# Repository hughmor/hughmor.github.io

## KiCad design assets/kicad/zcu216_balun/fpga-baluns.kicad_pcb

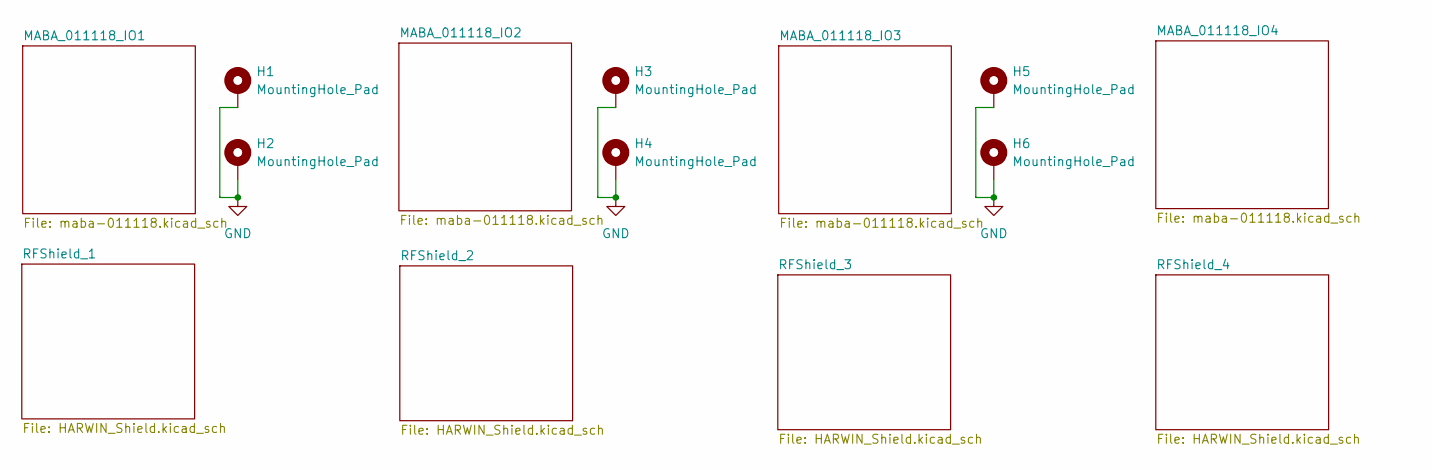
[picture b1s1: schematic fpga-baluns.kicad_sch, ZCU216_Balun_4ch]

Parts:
H1, H2, H3, H4, H5, H6: MountingHole_Pad; MountingHole_3.2mm_M3_DIN965_Pad_TopOnly

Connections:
GND: H1.1, H2.1, H3.1, H4.1, H5.1, H6.1; also elsewhere on the board

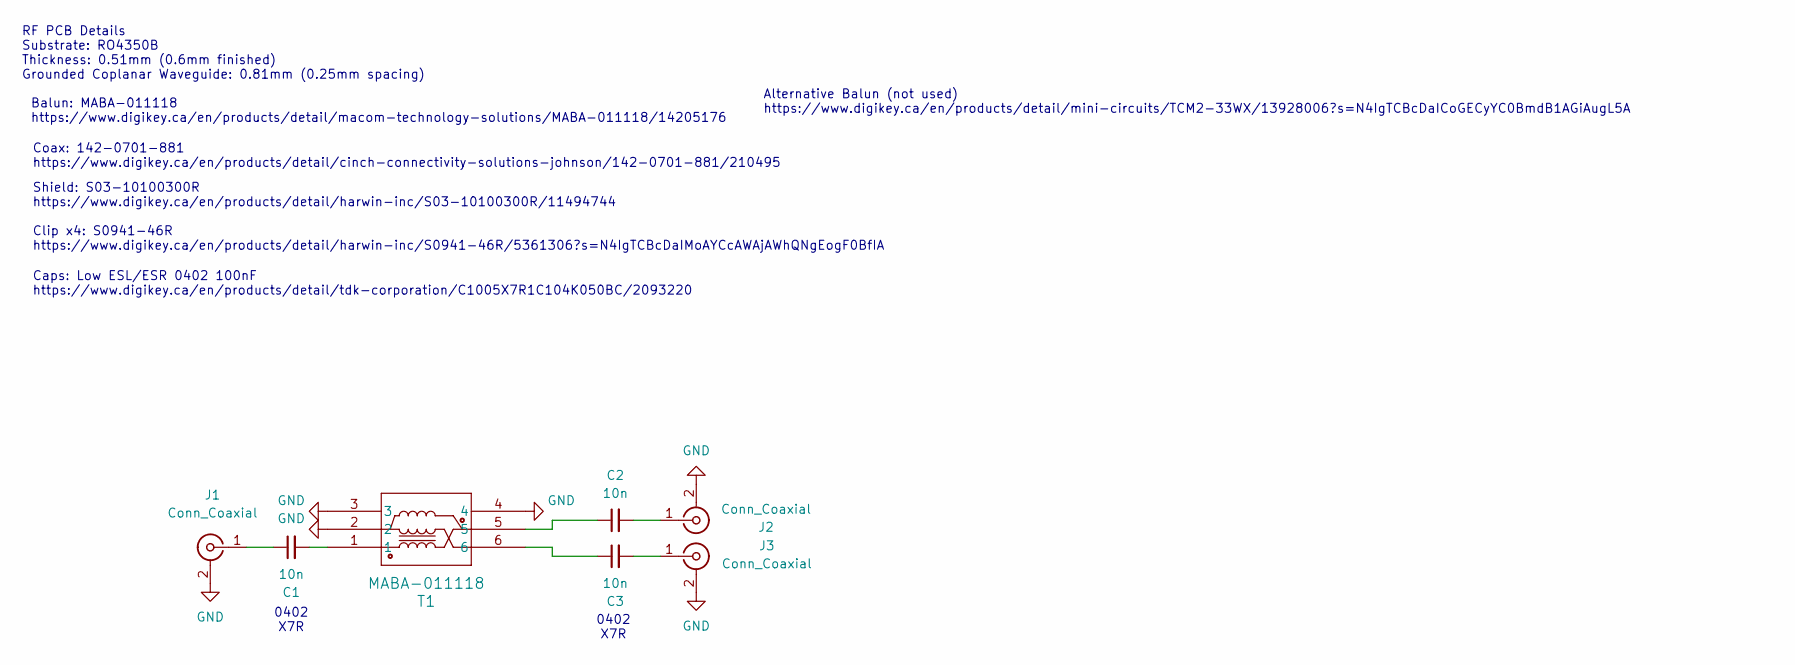
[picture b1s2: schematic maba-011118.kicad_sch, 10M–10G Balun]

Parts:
C1, C2, C3: 10n; C_0402_1005Metric; LCSC Part # C3855387
J1, J2, J3: Conn_Coaxial; SMA_Molex_73251-1153_EdgeMount_Horizontal_Custom
T1: MABA-011118; MABA-011118_MCM; LCSC Part # C50327609

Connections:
GND: J1.2 (Ext), J2.2 (Ext), J3.2 (Ext), T1.2, T1.3, T1.4; also elsewhere on the board
unnamed: C1.2, T1.1
unnamed: C2.1, T1.5
unnamed: C3.1, T1.6
unnamed: C1.1, J1.1 (In)
unnamed: C2.2, J2.1 (In)
unnamed: C3.2, J3.1 (In)

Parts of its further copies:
C4, C5, C6, C7, C8, C9, C10, C11, C12: 10n; C_0402_1005Metric; LCSC Part # C3855387
J4, J5, J6, J7, J8, J9, J10, J11, J12: Conn_Coaxial; SMA_Molex_73251-1153_EdgeMount_Horizontal_Custom
T2, T3, T4: MABA-011118; MABA-011118_MCM; LCSC Part # C50327609

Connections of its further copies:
GND: J4.2 (Ext), J5.2 (Ext), J6.2 (Ext), J7.2 (Ext), J8.2 (Ext), J9.2 (Ext), J10.2 (Ext), J11.2 (Ext), J12.2 (Ext), T2.2, T2.3, T2.4, T3.2, T3.3, T3.4, T4.2, T4.3, T4.4; also elsewhere on the board
unnamed: C4.2, T2.1
unnamed: C5.1, T2.5
unnamed: C6.1, T2.6
unnamed: C7.2, T3.1
unnamed: C8.1, T3.5
unnamed: C9.1, T3.6
unnamed: C10.2, T4.1
unnamed: C11.1, T4.5
unnamed: C12.1, T4.6
unnamed: C4.1, J4.1 (In)
unnamed: C5.2, J5.1 (In)
unnamed: C6.2, J6.1 (In)
unnamed: C7.1, J7.1 (In)
unnamed: C8.2, J8.1 (In)
unnamed: C9.2, J9.1 (In)
unnamed: C10.1, J10.1 (In)
unnamed: C11.2, J11.1 (In)
unnamed: C12.2, J12.1 (In)

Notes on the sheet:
0402 X7R
Alternative Balun (not used) https://www.digikey.ca/en/products/detail/mini-circuits/TCM2-33WX/13928006?s=N4IgTCBcDaICoGECyYC0BmdB1AGiAugL5A
Balun: MABA-011118 https://www.digikey.ca/en/products/detail/macom-technology-solutions/MABA-011118/14205176
Coax: 142-0701-881 https://www.digikey.ca/en/products/detail/cinch-connectivity-solutions-johnson/142-0701-881/210495
RF PCB Details Substrate: RO4350B Thickness: 0.51mm (0.6mm finished) Grounded Coplanar Waveguide: 0.81mm (0.25mm spacing)
Caps: Low ESL/ESR 0402 100nF https://www.digikey.ca/en/products/detail/tdk-corporation/C1005X7R1C104K050BC/2093220
Shield: S03-10100300R https://www.digikey.ca/en/products/detail/harwin-inc/S03-10100300R/11494744 Clip x4: S0941-46R https://www.digikey.ca/en/products/detail/harwin-inc/S0941-46R/5361306?s=N4IgTCBcDaIMoAYCcAWAjAWhQNgEogF0BfIA

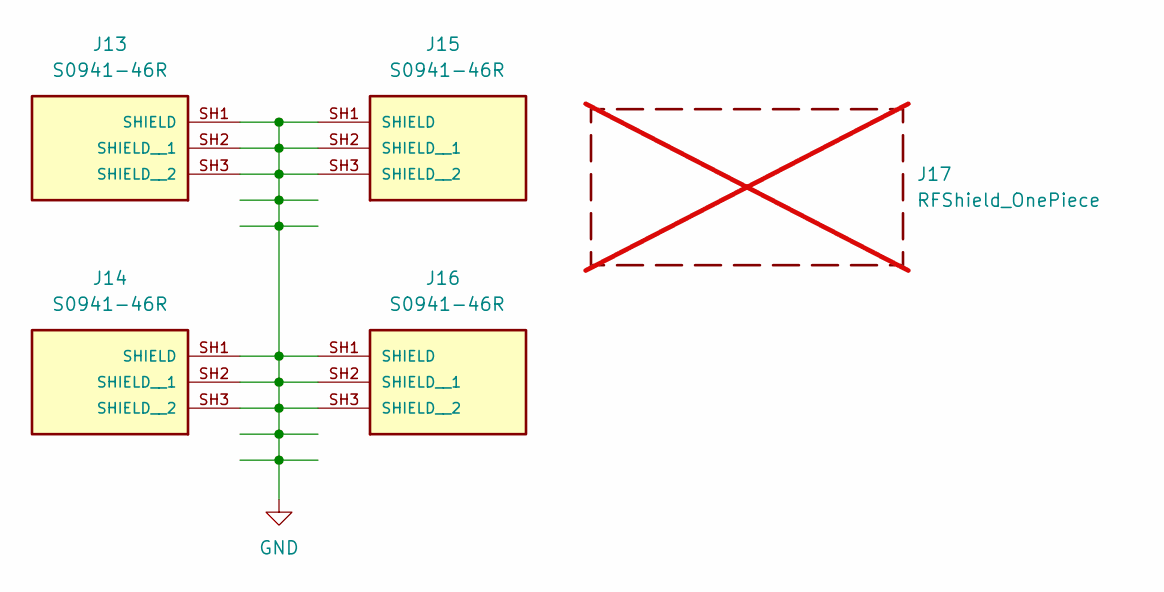
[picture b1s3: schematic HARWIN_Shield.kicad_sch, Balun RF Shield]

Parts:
J13, J14, J15, J16: S0941-46R; HARWIN_S1001-46R; PARTREV 5; LCSC Part # C5440762
J17: RFShield_OnePiece; HARWIN_S03_10100300R; not fitted

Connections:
GND: J13.SH1 (SHIELD), J13.SH2 (SHIELD__1), J13.SH3 (SHIELD__2), J14.SH1 (SHIELD), J14.SH2 (SHIELD__1), J14.SH3 (SHIELD__2), J15.SH1 (SHIELD), J15.SH2 (SHIELD__1), J15.SH3 (SHIELD__2), J16.SH1 (SHIELD), J16.SH2 (SHIELD__1), J16.SH3 (SHIELD__2); also elsewhere on the board

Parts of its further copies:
J18, J19, J20, J21, J23, J24, J25, J26, J28, J29, J30, J31: S0941-46R; HARWIN_S1001-46R; PARTREV 5; LCSC Part # C5440762
J22, J27, J32: RFShield_OnePiece; HARWIN_S03_10100300R; not fitted

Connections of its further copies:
GND: J18.SH1 (SHIELD), J18.SH2 (SHIELD__1), J18.SH3 (SHIELD__2), J19.SH1 (SHIELD), J19.SH2 (SHIELD__1), J19.SH3 (SHIELD__2), J20.SH1 (SHIELD), J20.SH2 (SHIELD__1), J20.SH3 (SHIELD__2), J21.SH1 (SHIELD), J21.SH2 (SHIELD__1), J21.SH3 (SHIELD__2), J23.SH1 (SHIELD), J23.SH2 (SHIELD__1), J23.SH3 (SHIELD__2), J24.SH1 (SHIELD), J24.SH2 (SHIELD__1), J24.SH3 (SHIELD__2), J25.SH1 (SHIELD), J25.SH2 (SHIELD__1), J25.SH3 (SHIELD__2), J26.SH1 (SHIELD), J26.SH2 (SHIELD__1), J26.SH3 (SHIELD__2), J28.SH1 (SHIELD), J28.SH2 (SHIELD__1), J28.SH3 (SHIELD__2), J29.SH1 (SHIELD), J29.SH2 (SHIELD__1), J29.SH3 (SHIELD__2), J30.SH1 (SHIELD), J30.SH2 (SHIELD__1), J30.SH3 (SHIELD__2), J31.SH1 (SHIELD), J31.SH2 (SHIELD__1), J31.SH3 (SHIELD__2); also elsewhere on the board

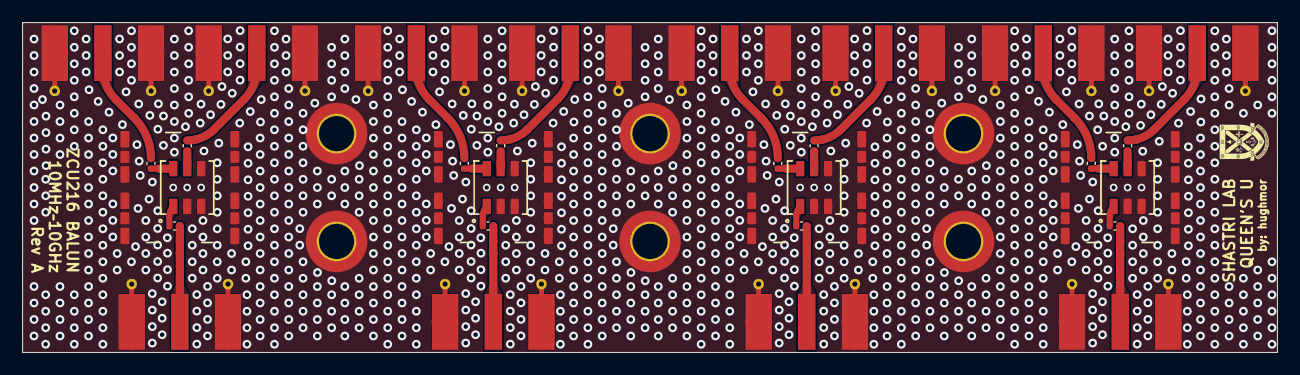
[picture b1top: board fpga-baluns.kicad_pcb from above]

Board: 2 copper layers, 114.1 x 30.0 mm, 54 parts (0 on the bottom side), 25 nets.

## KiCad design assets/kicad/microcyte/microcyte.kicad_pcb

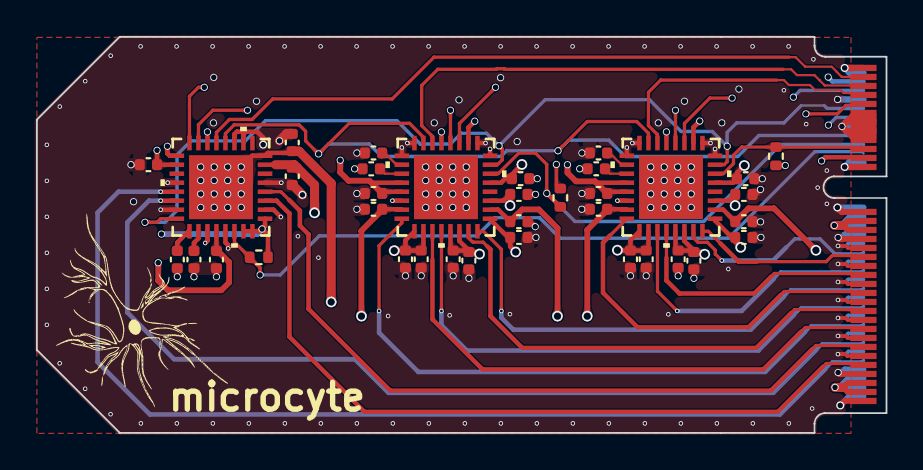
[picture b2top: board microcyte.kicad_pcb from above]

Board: 6 copper layers, 47.2 x 22.0 mm, 37 parts (0 on the bottom side), 35 nets.

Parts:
C1, C3, C5: 47n; C_0402_1005Metric
C2, C4, C6, C16, C26, C29: 100n; C_0402_1005Metric
C7, C8, C9, C10, C11, C12, C13, C14, C15, C17, C18, C19, C20, C21, C22, C23, C24, C25, C27, C28, C30: 1u; C_0402_1005Metric
J1: Conn_02x38_Odd_Even; Connector_M.2_key-E
R1, R3, R5: 10k; R_0402_1005Metric
U1, U2: LTC2662HUH-12-PBF; 05-08-1693_ADI
U3: LTC2664HUH-12-PBF; 05-08-1693_ADI

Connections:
+5V: C15.1, C16.1, C25.1, C26.1, C29.1, C30.1, J1.4, J1.21, R1.1, R3.1, R5.1, U1.2 (TGP), U1.12 (FSADJ), U1.13 (VCC), U1.29 (IOVCC), U2.2 (TGP), U2.12 (FSADJ), U2.13 (VCC), U2.29 (IOVCC), U3.1 (MSP2), U3.17 (TGP), U3.18 (IOVCC), U3.28 (VCC), U3.31 (MSP0), U3.32 (MSP1)
+10V: C7.1, C8.1, C9.1, C10.1, C11.1, C12.1, C17.1, C18.1, C19.1, C20.1, C21.1, C22.1, C27.1, J1.34, J1.35, J1.36, J1.37, U1.17 (VDD4), U1.18 (VDD3), U1.21 (VDD2), U1.22 (VDD1), U1.25 (VDD0), U1.27 (V+), U2.17 (VDD4), U2.18 (VDD3), U2.21 (VDD2), U2.22 (VDD1), U2.25 (VDD0), U2.27 (V+), U3.7 (V+)
-10V: C13.1, C14.1, C23.1, C24.1, C28.1, J1.70, J1.71, J1.72, J1.73, U1.15 (V-), U1.26 (V-), U2.15 (V-), U2.26 (V-), U3.8 (V), U3.33 (EPAD)
CLR: J1.10, U1.31 (*CLR), U2.31 (*CLR), U3.24 (*CLR)
FAULT1: J1.19, R3.2, U1.30 (*FAULT)
FAULT2: J1.18, R1.2, U2.30 (*FAULT)
GND: C1.2, C2.2, C3.2, C4.2, C5.2, C6.2, C7.2, C8.2, C9.2, C10.2, C11.2, C12.2, C13.2, C14.2, C15.2, C16.2, C17.2, C18.2, C19.2, C20.2, C21.2, C22.2, C23.2, C24.2, C25.2, C26.2, C27.2, C28.2, C29.2, C30.2, J1.1, J1.2, J1.8, J1.11, J1.13, J1.14, J1.15, J1.17, J1.22, J1.23, J1.32, J1.33, J1.38, J1.39, J1.40, J1.41, J1.44, J1.45, J1.48, J1.49, J1.52, J1.53, J1.56, J1.57, J1.60, J1.61, J1.64, J1.65, J1.68, J1.69, J1.74, J1.75, U1.1 (GND), U1.8 (GND), U1.9 (REFLO), U1.14 (GND), U1.32 (GND), U1.33 (GND), U2.1 (GND), U2.8 (GND), U2.9 (REFLO), U2.14 (GND), U2.32 (GND), U2.33 (GND), U3.2 (MUXIN0), U3.5 (MUXIN1), U3.10 (REFLO), U3.11 (GND), U3.20 (MUXIN2), U3.23 (MUXIN3), U3.27 (REFLO), U3.29 (GND)
I0: J1.43, U1.24 (OUT0)
I1: J1.42, U1.23 (OUT1)
I2: J1.47, U1.20 (OUT2)
I3: J1.46, U1.19 (OUT3)
I4: J1.51, U1.16 (OUT4)
I5: J1.50, U2.24 (OUT0)
I6: J1.55, U2.23 (OUT1)
I7: J1.54, U2.20 (OUT2)
I8: J1.59, U2.19 (OUT3)
I9: J1.58, U2.16 (OUT4)
LDAC: J1.16, U1.7 (*LDAC), U2.7 (*LDAC), U3.12 (*LDAC)
MISO: J1.9, U1.4 (SDO), U2.4 (SDO), U3.15 (SDO)
MOSI: J1.6, U1.3 (SDI), U2.3 (SDI), U3.16 (SDI)
unnamed: C3.1, U1.10 (REF)
unnamed: C4.1, U1.11 (REFCOMP)
unnamed: C5.1, U2.10 (REF)
unnamed: C6.1, U2.11 (REFCOMP)
unnamed: C1.1, U3.25 (REF)
unnamed: C2.1, U3.26 (REFCOMP)
SCLK: J1.12, U1.5 (SCK), U2.5 (SCK), U3.14 (SCK)
SS1: J1.7, U1.6 (*CS/LD)
SS2: J1.5, U2.6 (*CS/LD)
SS3: J1.3, U3.13 (*CS/LD)
TEMP: J1.20, R5.2, U3.30 (*OVRTMP)
Vb0: J1.67, U3.3 (VOUT0)
Vb1: J1.63, U3.4 (VOUT1)
Vb2: J1.66, U3.21 (VOUT2)
Vb3: J1.62, U3.22 (VOUT3)

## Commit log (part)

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2022-03-10 customized config file
2022-03-10 Create CNAME
2022-03-12 Update CNAME
2022-03-12 update gitignore for local dev
2022-03-12 removed unpopulated sections from navigation bar
2022-03-12 updated sidebar and added avatar
2022-03-12 configured about page
2022-03-13 uploaded CV
2022-03-13 quick fix to activities in bio
2022-04-26 updated images
2022-04-26 updated about me page
2022-04-26 temporarily removed twitter
2022-04-26 correcting emoji syntax
2022-04-26 edited about me
2022-04-26 about me: emphasize chip layout
2022-04-26 updated resume
2022-04-26 updated resume link on CV page
2023-02-04 added icons
2023-02-04 modified profile photo
2023-02-04 fixed 150 icon
2023-02-04 png profile photo
2023-02-04 testing equations
2023-02-04 added first publication
2023-02-04 updated cv page
2023-02-04 remnoved dedicated teaching section from cv page
2023-02-04 hotfix: formatting
2023-02-04 updated about page
2023-02-04 removed teaching section; added blog section
2023-02-04 removed default blog postst
2023-02-04 renamed blog page
2023-02-04 updated sidebar description
2023-02-04 updated sidebar
2023-02-04 remove sidebar from blog
2023-02-04 added about to navigation bar
2024-05-10 added dot plan embedded from google docs at /plan
2025-06-10 upload all local edits
2025-06-12 fresh start
2025-06-16 new stripped down site version
2025-06-16 katex math option
2025-06-16 added latex support
2025-06-16 updated dgemv post
2025-07-10 added socials icons
2025-09-15 updated website colours
2025-09-15 updated bio
2025-09-16 post on tAoDSaE
2025-09-16 update bio and config
2025-09-18 added dates to posts
2025-09-18 added social.html
